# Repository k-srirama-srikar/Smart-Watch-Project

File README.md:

# Smart Watch ⌚
By:<br>
- [Parmar Raagam Hitesh](https://github.com/Raagam-Parmar) (112301024)
- [M Murali Karthick](https://github.com/Murali47k) (112301019)
- [M Sreenath Karthick](https://github.com/SreenathKarthick11) (112301042)
- [K Srirama Srikar](https://github.com/k-srirama-srikar) (142301013)

We developed a smart watch as a part of The Robotics Club, IIT Palakkad, during the Spring (Even) Semester 2024...<br>
I, along with Murali Karthick, wrote the code for the OLED and the design of the case and the PCBs were done by Raagam Parmar and Sreenath Karthick...<br>

### Components used
- ATMega328p
- DS3231M-RTC(Real Time Clock)
- LM7805 (Voltage Regulator)
- SSD1306 (OLED)
- A LiPo battery

Click [here](https://wokwi.com/projects/405116825999428609) to see a Wokwi simulation of the project...

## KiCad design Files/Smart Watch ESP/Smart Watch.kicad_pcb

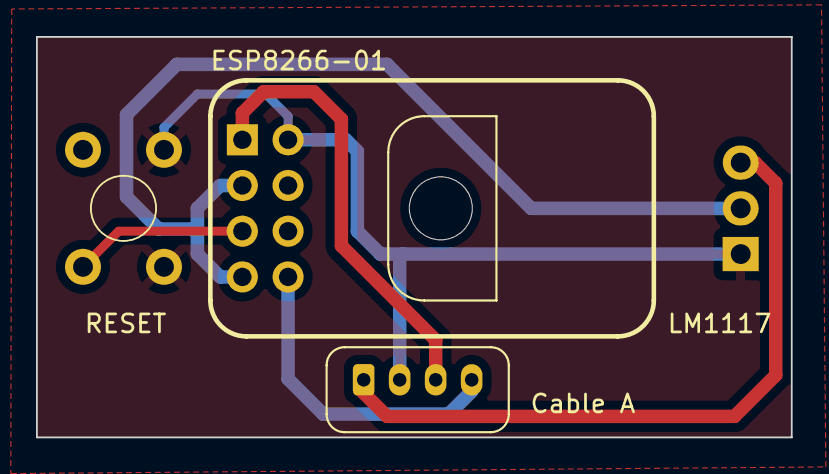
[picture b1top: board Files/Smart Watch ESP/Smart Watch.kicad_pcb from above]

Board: 2 copper layers, 41.9 x 22.3 mm, 4 parts (0 on the bottom side), 6 nets.

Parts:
J4: Conn_01x04_Socket; JST_PH_B4B-PH-K_1x04_P2.00mm_Vertical_Simple
S1: RESET; SW_PUSH_6mm_h5mm_Simple
U3: ESP-01v090; ESP-01_Simple
U4: LM1117T-3.3; TO-220-3_Horizontal_TabDown_Simple

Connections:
+3.3V: U3.3 (CH_PD), U3.7 (VCC), U4.2 (VO)
+5V: J4.1, U4.3 (VI)
Earth: J4.2, S1.2 (PIN2), U3.2 (GND), U4.1 (GND)
unnamed: S1.1 (PIN1), U3.5 (RST)
ardR_espT: J4.3, U3.1 (UTXD)
ardT_espR: J4.4, U3.8 (URXD)

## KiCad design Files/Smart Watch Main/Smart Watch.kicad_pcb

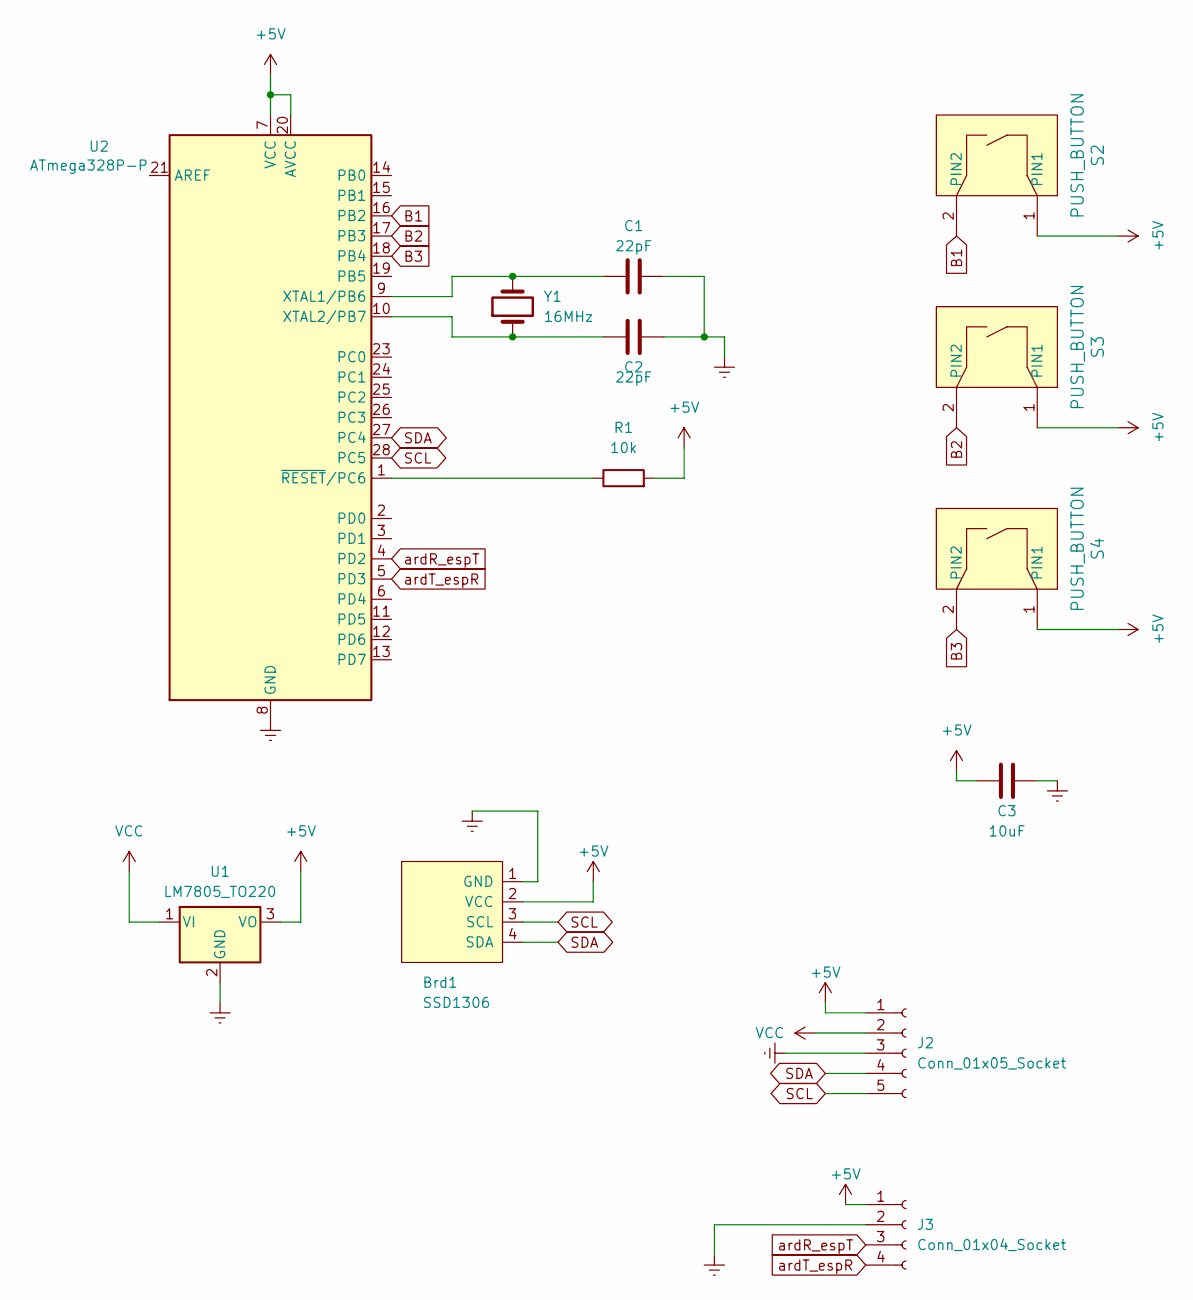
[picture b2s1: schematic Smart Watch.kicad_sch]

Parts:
Brd1: SSD1306; 128x64OLED
C1, C2: 22pF; C_Disc_D5.1mm_W3.2mm_P5.00mm
C3: 10uF; C_Disc_D5.1mm_W3.2mm_P5.00mm
J2: Conn_01x05_Socket; JST_PH_B5B-PH-K_1x05_P2.00mm_Vertical
J3: Conn_01x04_Socket; JST_PH_B4B-PH-K_1x04_P2.00mm_Vertical
R1: 10k; R_Axial_DIN0207_L6.3mm_D2.5mm_P10.16mm_Horizontal
S2, S3, S4: PUSH_BUTTON; SW_PUSH_6mm_h5mm
U1: LM7805_TO220; TO-220-3_Horizontal_TabDown
U2: ATmega328P-P; DIP-28_W7.62mm
Y1: 16MHz; Crystal_HC49-U_Vertical

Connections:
+5V: Brd1.2 (VCC), C3.1, J2.1, J3.1, R1.2, S2.1 (PIN1), S3.1 (PIN1), S4.1 (PIN1), U1.3 (VO), U2.7 (VCC), U2.20 (AVCC)
B1: S2.2 (PIN2), U2.16 (PB2)
B2: S3.2 (PIN2), U2.17 (PB3)
B3: S4.2 (PIN2), U2.18 (PB4)
Earth: Brd1.1 (GND), C1.2, C2.2, C3.2, J2.3, J3.2, U1.2 (GND), U2.8 (GND), U2.22 (GND)
unnamed: C1.1, U2.9 (XTAL1/PB6), Y1.2
unnamed: C2.1, U2.10 (XTAL2/PB7), Y1.1
unnamed: R1.1, U2.1 (~RESET/PC6)
SCL: Brd1.3 (SCL), J2.5, U2.28 (PC5)
SDA: Brd1.4 (SDA), J2.4, U2.27 (PC4)
VCC: J2.2, U1.1 (VI)
ardR_espT: J3.3, U2.4 (PD2)
ardT_espR: J3.4, U2.5 (PD3)

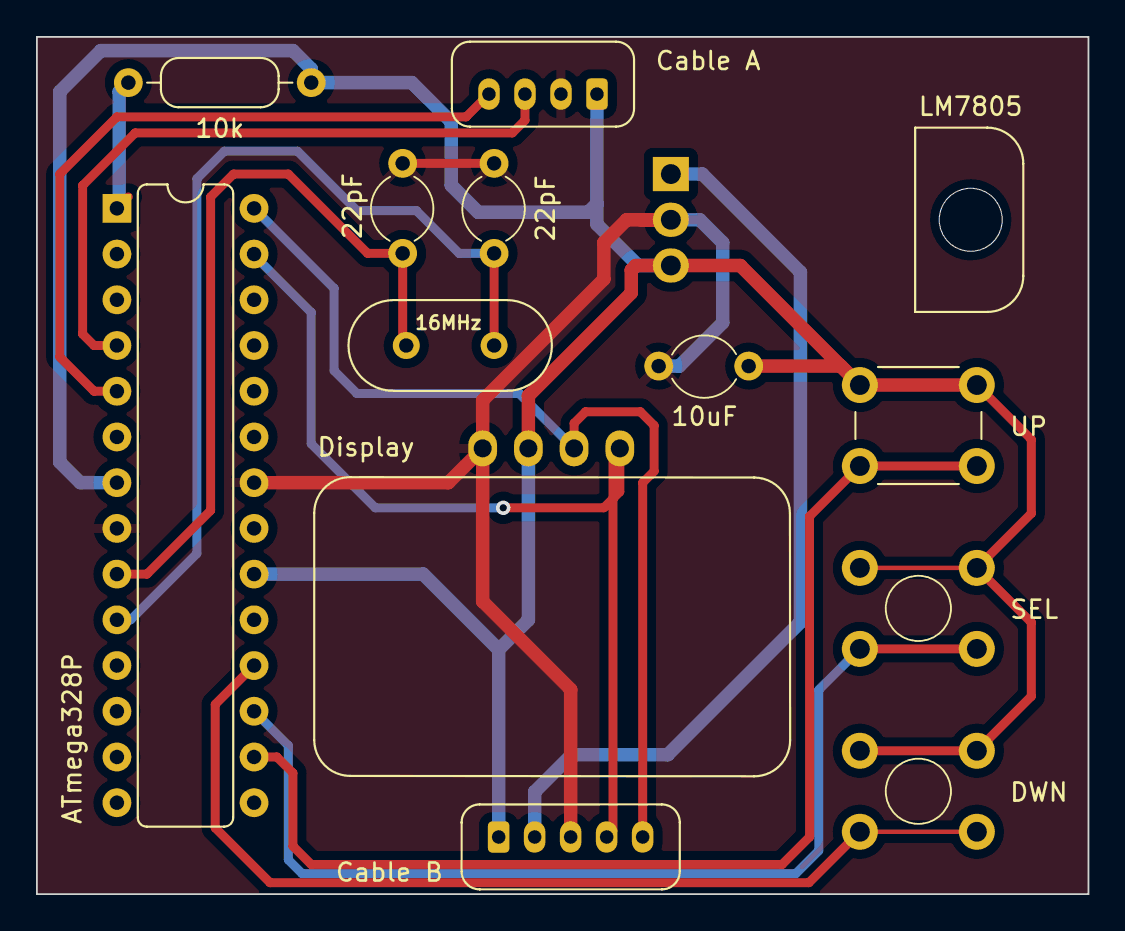
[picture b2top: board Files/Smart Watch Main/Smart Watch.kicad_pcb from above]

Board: 2 copper layers, 58.4 x 47.6 mm, 13 parts (0 on the bottom side), 13 nets.

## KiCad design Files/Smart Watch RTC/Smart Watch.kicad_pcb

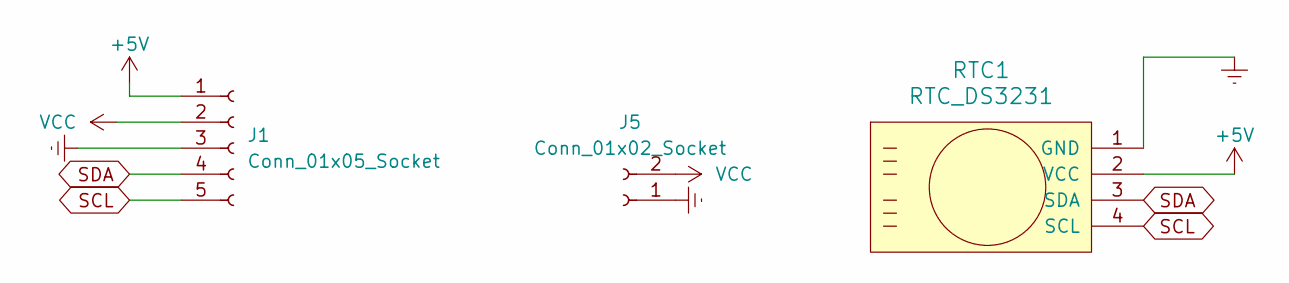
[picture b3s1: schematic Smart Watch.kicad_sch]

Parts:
J1: Conn_01x05_Socket; JST_PH_B5B-PH-K_1x05_P2.00mm_Vertical
J5: Conn_01x02_Socket; JST_PH_B2B-PH-K_1x02_P2.00mm_Vertical
RTC1: RTC_DS3231

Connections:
+5V: J1.1, RTC1.2 (VCC)
Earth: J1.3, J5.1, RTC1.1 (GND)
SCL: J1.5, RTC1.4 (SCL)
SDA: J1.4, RTC1.3 (SDA)
VCC: J1.2, J5.2

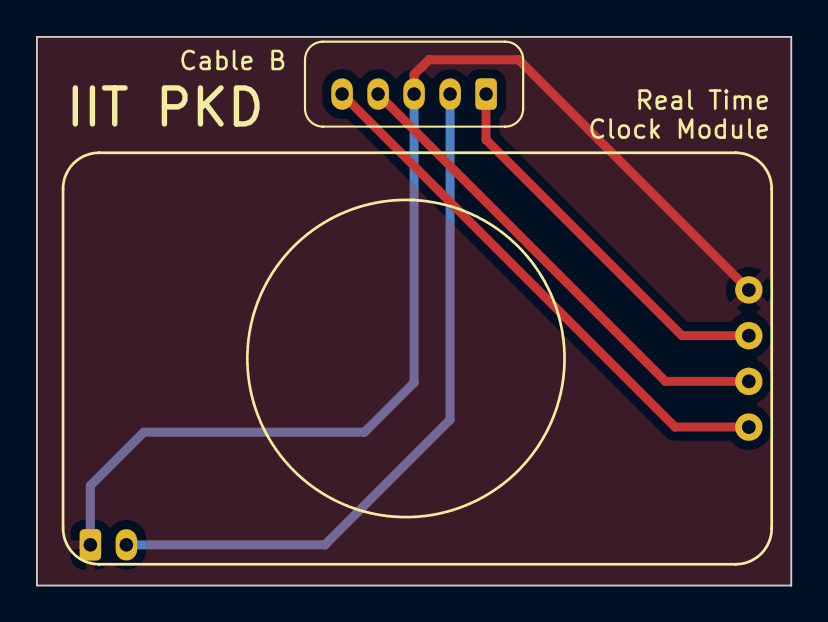
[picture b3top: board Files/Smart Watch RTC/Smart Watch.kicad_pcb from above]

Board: 2 copper layers, 41.9 x 30.5 mm, 3 parts (0 on the bottom side), 5 nets.
